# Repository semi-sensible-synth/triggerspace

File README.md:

# triggerspace

> **TESTED** - v0.042 works with some simple bodges (build notes below)
>
> **IN PROGRESS** - v0.5.0 removes the v0.042 bodges and adds optional RC reconstruction-cap
> sockets on the jack PCB's outputs to support alternative oscillators/sampler firmware; not yet fabricated or bench-verified (see
> [CHANGELOG.md](CHANGELOG.md))

This is a remix of the [NanoGris](https://github.com/Quinienl/NanoGris) trigger sequence generator (by Quinie), which in turn was based on the original [Grids](https://pichenettes.github.io/mutable-instruments-documentation/modules/grids/) hardware design by Mutable Instruments / Émilie Gillet, used under a Creative Commons ShareAlike 3.0 License (CC BY-SA 3.0).

The front panel looks something like this:

# Features
- Outputs three channels of 'topographic' drum triggers (kick, snare, hihat), with accent outputs
- Internal clock, with reset and swing
- External clock input, via triggers or MIDI clock
- Beat density (fill), X, Y and Chaos inputs to modify each pattern
- MIDI TRS-A output, General MIDI drum notes on channel 10
- MIDI TRS input accepts Type A and Type B (v0.5.0, [LPZW auto-crossover MIDI input](https://github.com/kay-lpzw/LPZW_TRS_MIDI))
- 38mA peak current draw on +12V rail (28mA idle)
- Experimental alternative firmwares: 6-voice oscillator [Gritty-osc](https://github.com/semi-sensible-synth/triggerspace/blob/main/firmware/Gritty-osc/README.md) and drum hit synth [Gritty-drumsynth](https://github.com/semi-sensible-synth/triggerspace/blob/main/firmware/Gritty-drumsynth/README.md)

## Firmware

_The stock Grids/NanoGris firmware is not compatible_ - use this: [Gritty-Grids firmware (triggerspace fork)](https://github.com/semi-sensible-synth/Gritty-Grids). Follow the instructions there to flash the firmware to your triggerspace module.

This Gritty-Grids fork:

- Supports modified Arduino Nano pin assignments used by _triggerspace_ hardware
- Sends General MIDI drum notes on channel 10 to MIDI-OUT (TRS-A)
  - GM MIDI (and Roland TR-8S) drum note numbers:
  ```
  Out 1:             36 (0x24, C1)  - bass/kick drum
  Out 2:             38 (0x26, D1)  - snare drum
  Out 3 (no accent): 42 (0x2a, F#1) - closed hi-hat
  Out 3 (accented):  46 (0x2e, Bb1) - open hi-hat
  ```
- Maps accents to MIDI note velocity: accented steps are sent at velocity 127 and
  unaccented steps at 90. Accented hi-hat steps also switch to the open hi-hat note (46).
  - Accents only exist in drum mode. With the clock output option on, Grids
    has a single common accent output, so that accent applies to all three drums.
  - In Euclidean mode there are no accents: every note is sent at velocity 127 as the
    closed hi-hat.
  - Set by `midi_accent_velocity` in `grids/grids.cc` (default on). When off, every note
    is sent at 127; the open/closed hi-hat switch still follows the accent. It can only
    be changed by recompiling for now.
  - Gritty-drumsynth sends MIDI notes the same way.

## Build options

### MIDI IN optocoupler (U8 / U9)

From v0.5.0 the MIDI input is the
[LPZW auto-crossover MIDI input](https://github.com/kay-lpzw/LPZW_TRS_MIDI) by Kay Knofe
of LPZW.modules.

It accepts TRS Type A and Type B cables with no switch. It works by using the two LEDs of a dual optocoupler in an 'anti-parallel' configuration across the tip and ring, each with its own 220R. Whichever way round the loop current flows, one LED lights, and the two open-collector outputs share one 1k pull-up (R47), so the Nano sees the same signal either way.

Fit one of these:

| Build | U8 (DIP-8 socket) | U9 (SOIC-8) | D7 | JP3, JP4 | Accepts |
|---|---|---|---|---|---|
| **Default** | HCPL-2630 or HCPL-2631 | not fitted | not fitted | as made (1-2 bridged) | Type A and B |
| SMD optocoupler | not fitted, no socket | HCPL-0630 or HCPL-0631 | not fitted | as made (1-2 bridged) | Type A and B |
| 6N138 (as v0.042) | 6N138 | not fitted | 1N4148 | cut 1-2, bridge 2-3 | Type A only |

- U9 sits inside U8's DIP-8 footprint on the back of the jack PCB, so fit U8 or U9,
  never both - a DIP socket would sit on top of U9. The HCPL-263x (DIP-8) and HCPL-063x
  (SOIC-8) have the same pinout.
- R46 (4.7k) is fitted in every build but only connected (through JP4) in the 6N138
  build, where it is the 6N138's base resistor. R51 is only used by the dual
  optocouplers; with a 6N138 it goes to an unconnected pin.
- D7 protects the 6N138's LED from reverse voltage. Don't fit it with a dual
  optocoupler: it would sit across one of the LEDs and take the current meant for the
  other, so Type B input would stop working.
- The HCPL-263x/063x is guaranteed to switch at 5mA LED current. A 5V MIDI 1.0 sender
  into a 220R receiver gives about 5mA, so worst-case parts are marginal (typical parts
  switch at about 2mA); 3.3V senders built to the MIDI Association's CA-33 values give
  about 7mA. The 6N138 needs only about 1.6mA, so it tolerates weaker Type A senders.

See [Jumpers](#jumpers) for JP3/JP4 to enable the 6N138 build (and other jumper settings).

### -5V reference: LM4040 or 5.1V zener (U5 / D8)

U5 (LM4040LP-5, TO-92) makes the -5V reference (`ref_5`) for the CV input offsets,
fed from -12V through R31 (10k). D8 is an alternative footprint in parallel with it for
a 5.1V zener diode (DO-35, e.g. BZX79C5V1 or 1N5231B), which worked well on a v0.042
build. Fit U5 or D8, not both.

- D8 sits inside U5's outline and is mounted upright: the diode body goes on the round
  pad with the cathode band at the top, and the bent lead goes into the square pad
  (marked K, to GND). The anode is on `ref_5`, because the reference is negative.
- R31 sets the zener current to about (12V - 5.1V) / 10k = 0.7mA. This is below the
  5-20mA test current of common 5.1V zeners, so expect a little less than 5.1V and a
  less stable voltage than the LM4040. The voltage shifts the CV input offsets slightly;
  it doesn't affect the triggers.

### +5V supply and power header (U4, JP5, JP6, J12)

The +5V rail (op amps, shift register, pots, trigger transistors) can come from one of
three sources. Use exactly one: don't connect two regulator outputs together.

| +5V source | U4, C11, C12 | JP5 | JP6 | Power cable |
|---|---|---|---|---|
| **U4 (L7805), default** | fitted | open | open | 10-pin or 16-pin |
| Nano's regulator | not fitted | bridged | open | 10-pin or 16-pin |
| Eurorack +5V | not fitted | open | bridged | 16-pin, from a PSU with +5V |

U4, C11 and C12 are marked "OPTIONAL" on the silkscreen. JP5 and JP6 are open as made.

- **Nano's regulator (JP5):** since v0.5.0 the Nano's VIN is fed from +12V, so its
  onboard 5V regulator is running anyway. JP5 connects the Nano's 5V pin (A1 pin 27) to
  the +5V rail, so that regulator supplies the whole module. The v0.042 module drew
  28-38mA from +12V in total, so the regulator dissipates about (12V - 5V) x 38mA =
  0.27W. With JP5 bridged, the Nano's USB port also powers the +5V rail when the module
  has no Eurorack power.
- **Eurorack +5V (JP6):** J12 is a 16-pin (2x8) footprint. Pins 11 and 12 are the
  Eurorack +5V rail, connected to the module's +5V rail through JP6. Pins 13-16 (CV and
  Gate buses) are not connected. With JP6 open, a 16-pin cable is safe whether or not
  the PSU provides +5V.
- **10-pin header in the 16-pin footprint:** a 2x5 header fits in J12 pins 1-10 (the
  end with the square pad, marked "RED!!" for the cable's -12V stripe), so 10-pin cables
  still work. The
  silkscreen outline is drawn for a 16-pin shrouded header; line up a 10-pin header's
  pin 1 with the square pad.

### RC reconstruction caps (CH*_CAP1)

The six 2-pin sockets next to the output jacks on the jack PCB (`CH1_CAP1`,
`CH1_ACC_CAP1`, `CH2_CAP1`, `CH2_ACC_CAP1`, `CH3_CAP1`, `CH3_ACC_CAP1`) take optional
capacitors to GND that filter the sigma-delta hiss from the Gritty-drumsynth firmware's
synthesised drum voices. Leave them empty for trigger outputs (Gritty-Grids firmware).
Values are still to be chosen (see TODO / IDEAS).

## Jumpers

Most solder jumpers (JP1-JP4) are shorted by a copper trace between their pads as made;
cut the trace with a craft knife to open them. JP5 and JP6 are open as made. Bridge pads
with solder to close a jumper. Pin
jumpers (J) are 2.54mm headers for jumper caps. Pin 1 of each header is the square pad.
The silkscreen next to each header repeats its settings.

Firmware and jack function settings, as shipped:

| Function | Gritty-Grids firmware (MIDI, default) | Stock Grids/NanoGris firmware (triggers) |
|---|---|---|
| Clock input to the Nano | JP2 bridged (clock on D8) | cut JP2, fit J2 (clock on D1) |
| Nano D1/TX | JP1 bridged (D1 drives MIDI OUT) | cut JP1, fit J1 (see below) |
| CLOCK / MIDI OUT jack | J6 1-2, J3 3-4 (optionally also J3 1-2) | J6 2-3, J3 1-2 |
| RND / MIDI IN jack | J8 2-3, J5 1-2, J4 3-4 | J8 1-2, J5 2-3, J4 1-2 |
| +5V source | U4 fitted, JP5 and JP6 open | same |

The jack settings are independent of the firmware: with Gritty-Grids you can still set
either jack back to a trigger output, and the MIDI clock or MIDI notes on that port are
then lost.

### Back PCB

- **JP1** (bridged) connects Nano D1/TX to the MIDI OUT line (`OUT_MIDI`, through R49
  to the jack). **JP2** (bridged) connects the clock input transistor (Q1) to D8. Both
  stay bridged for Gritty-Grids.
- **J1** connects D8 to the MIDI OUT line and **J2** connects the clock input to D1.
  The silkscreen instruction for stock firmware is "cut JP1 & JP2, bridge jumper J1,
  J2": the clock input then reaches D1, where the stock firmware reads it, and D1 is no
  longer connected to the MIDI OUT line. Don't fit J1 or J2 with JP1 and JP2 still
  bridged.
- **J5** (3-pin, to the RND / MIDI IN jack via the jack PCB): 1-2 = MIDI IN (optocoupler
  output to D0/RX), 2-3 = RND trigger output.
- **J6** (3-pin, to the CLOCK / MIDI OUT jack via the jack PCB): 1-2 = MIDI OUT (D1/TX
  through R49), 2-3 = CLOCK trigger output.
- **J9** (2-pin, silkscreen "MIDI IN" / "MIDI OUT"): pin 1 = D0/RX, pin 2 = D1/TX
  (logic level, before R49). Use it to wire up a different MIDI interface (e.g. a DIN
  socket board). If you feed a MIDI signal into pin 1, remove the J5 jumper so the
  optocoupler output doesn't drive the same line.
- **JP5** (open, below the Nano): bridge to power the +5V rail from the Nano's
  regulator. **JP6** (open, next to J12): bridge to power the +5V rail from the Eurorack
  +5V on a 16-pin cable. Fit U4, C11 and C12 only if both are open. See
  [+5V supply and power header](#5v-supply-and-power-header-u4-jp5-jp6-j12).

### Jack PCB

- **J3** (4-pin, CLOCK / MIDI OUT jack): 1-2 connects the sleeve to GND, 3-4 connects the
  ring to +5V through R50. CLOCK OUT: 1-2. MIDI OUT: 3-4; also fit 1-2 so the sleeve
  (cable shield) is grounded at the sending end, as the MIDI specification asks.
- **J4** (4-pin, RND / MIDI IN jack): 1-2 connects the sleeve to GND, 3-4 connects the
  ring to the optocoupler. RND OUT: 1-2. MIDI IN: 3-4 only; leave 1-2 open, since a MIDI
  receiver must not ground the cable shield.
- **J8** (3-pin, RND / MIDI IN jack tip): 1-2 = RND trigger output to the tip, 2-3 =
  optocoupler output to the back PCB (MIDI IN).
- **JP3** and **JP4** (3-pad solder jumpers, 1-2 bridged as made) select the MIDI IN
  optocoupler type. Leave them as made for the dual optocoupler (HCPL-263x in U8, or
  HCPL-063x in U9). For a 6N138, cut 1-2 and bridge 2-3 on both, and fit D7. See
  [MIDI IN optocoupler](#midi-in-optocoupler-u8--u9).
  - JP3 pad 2 goes to U8 pin 2 (HCPL-263x: LED 1 cathode; 6N138: LED anode). Pad 1 =
    jack ring (dual optocoupler), pad 3 = the R48 / D7 node (6N138).
  - JP4 pad 2 goes to U8 pin 7 (HCPL-263x: output 1; 6N138: transistor base). Pad 1 =
    the shared output and R47 pull-up (dual optocoupler), pad 3 = R46 4.7k to GND
    (6N138).

## Changelog

See [CHANGELOG.md](CHANGELOG.md) for the changes in each hardware revision.

## v0.042 build guide notes (bodges required !)

  - Trying to power the Nano via 5V from U4 voltage regulator to VIN pin 30 didn't work here, despite the original NanoGris design doing it this way. Upon reflection this is no surprise ... 5V isn't enough for the typical AMS1117-5.0 regulator found on a Nano (clone), which needs ~>= 6.5V input to work ! I fixed this with a bodge as follows:
    - Melt the VIN pin 30 solder joint and push it 'up' so it doesn't insert into the female header. This disconnects the Nano from the U4 regulator, but still allows U4 to power the 5V rail in the rest of the module.
    - Attach a bodge wire from the +12V rail pin on the U4 voltage regulator to the protruding VIN pin 30 (I used a single female header to make it easy to remove the Nano if required).
  - I didn't have an LM4040-5.0 on hand, but a 5.1V Zener diode seems to work well enough. From v0.5.0 it has its own footprint (D8, see [Build options](#build-options)).
  - Can optionally use an 78L50 (TO-92) voltage regulator rather than L7805 (TO-220)
  - Sometimes flashing the firmware seems to fail (can't connect to device) when the Nano is in the module, but seems to work if you take out out of the PCB to flash ¯\_(ツ)_/¯

## Modifications from the original NanoGris module

- Added MIDI-IN TRS-A jack + 6N137 optocoupler for MIDI clock sync. The original Grids always had this option as an extra jumper on the PCB - now it's broken out onto a more cluttered front panel !
- Added MIDI-OUT TRS-A - required changing the pin used for the clock in to allow use of hardware serial TX/RX, so this modules requires [custom firmware](https://github.com/semi-sensible-synth/Gritty-Grids) even if you aren't using the MIDI-OUT option.
  - I've added pin jumpers and cuttable solder jumpers to allow re-routing for stock firmware if required/desired.
- The CLOCK and RND outputs are repurposed as the TRS-A MIDI-OUT and MIDI-IN ports, respectively. Several pin jumpers can be used to choose if these act as MIDI ports or the original voltage-based trigger outputs.
- Made more space between the FILL knobs (closer to original Grids layout), use a tactile button and cap for TAP button, various tweaks to routing and front panel design

## TODO / IDEAS

- Fabricate and bench-verify v0.5.0.
- Choose the RC reconstruction-cap values (and confirm the socket footprint) by bench
  testing with the Gritty-drumsynth firmware.
- Bench-test the +5V supply options (JP5: Nano regulator, JP6: Eurorack +5V) without
  U4.
- Do we have room for mute switches/buttons on each channel ?
- Now that we are using a full 8x2 IDC power socket - can we also (optionally) connect the CV/GATE pins (eg to clock), or follow the Disting Select Bus protocol to use it for MIDI ?

### Future firmware ideas

- Disting Ex SD 6 Triggers mode, where notes span 48-53 (unaccented and accented)
- Chord/arp output over MIDI. Set the chord root/inversion to be played via one of the CV inputs, or MIDI-IN
  - Read MIDI notes from MIDI-IN, buffer the last 3 or 6 notes seen and play these for Out1-3, Accent 1-3
- (Crazier ideas: pair it with a SAM2695 or VS1053B based module/expander for GM MIDI audio out ! There seem to be NOS versions on AliExpress ....)

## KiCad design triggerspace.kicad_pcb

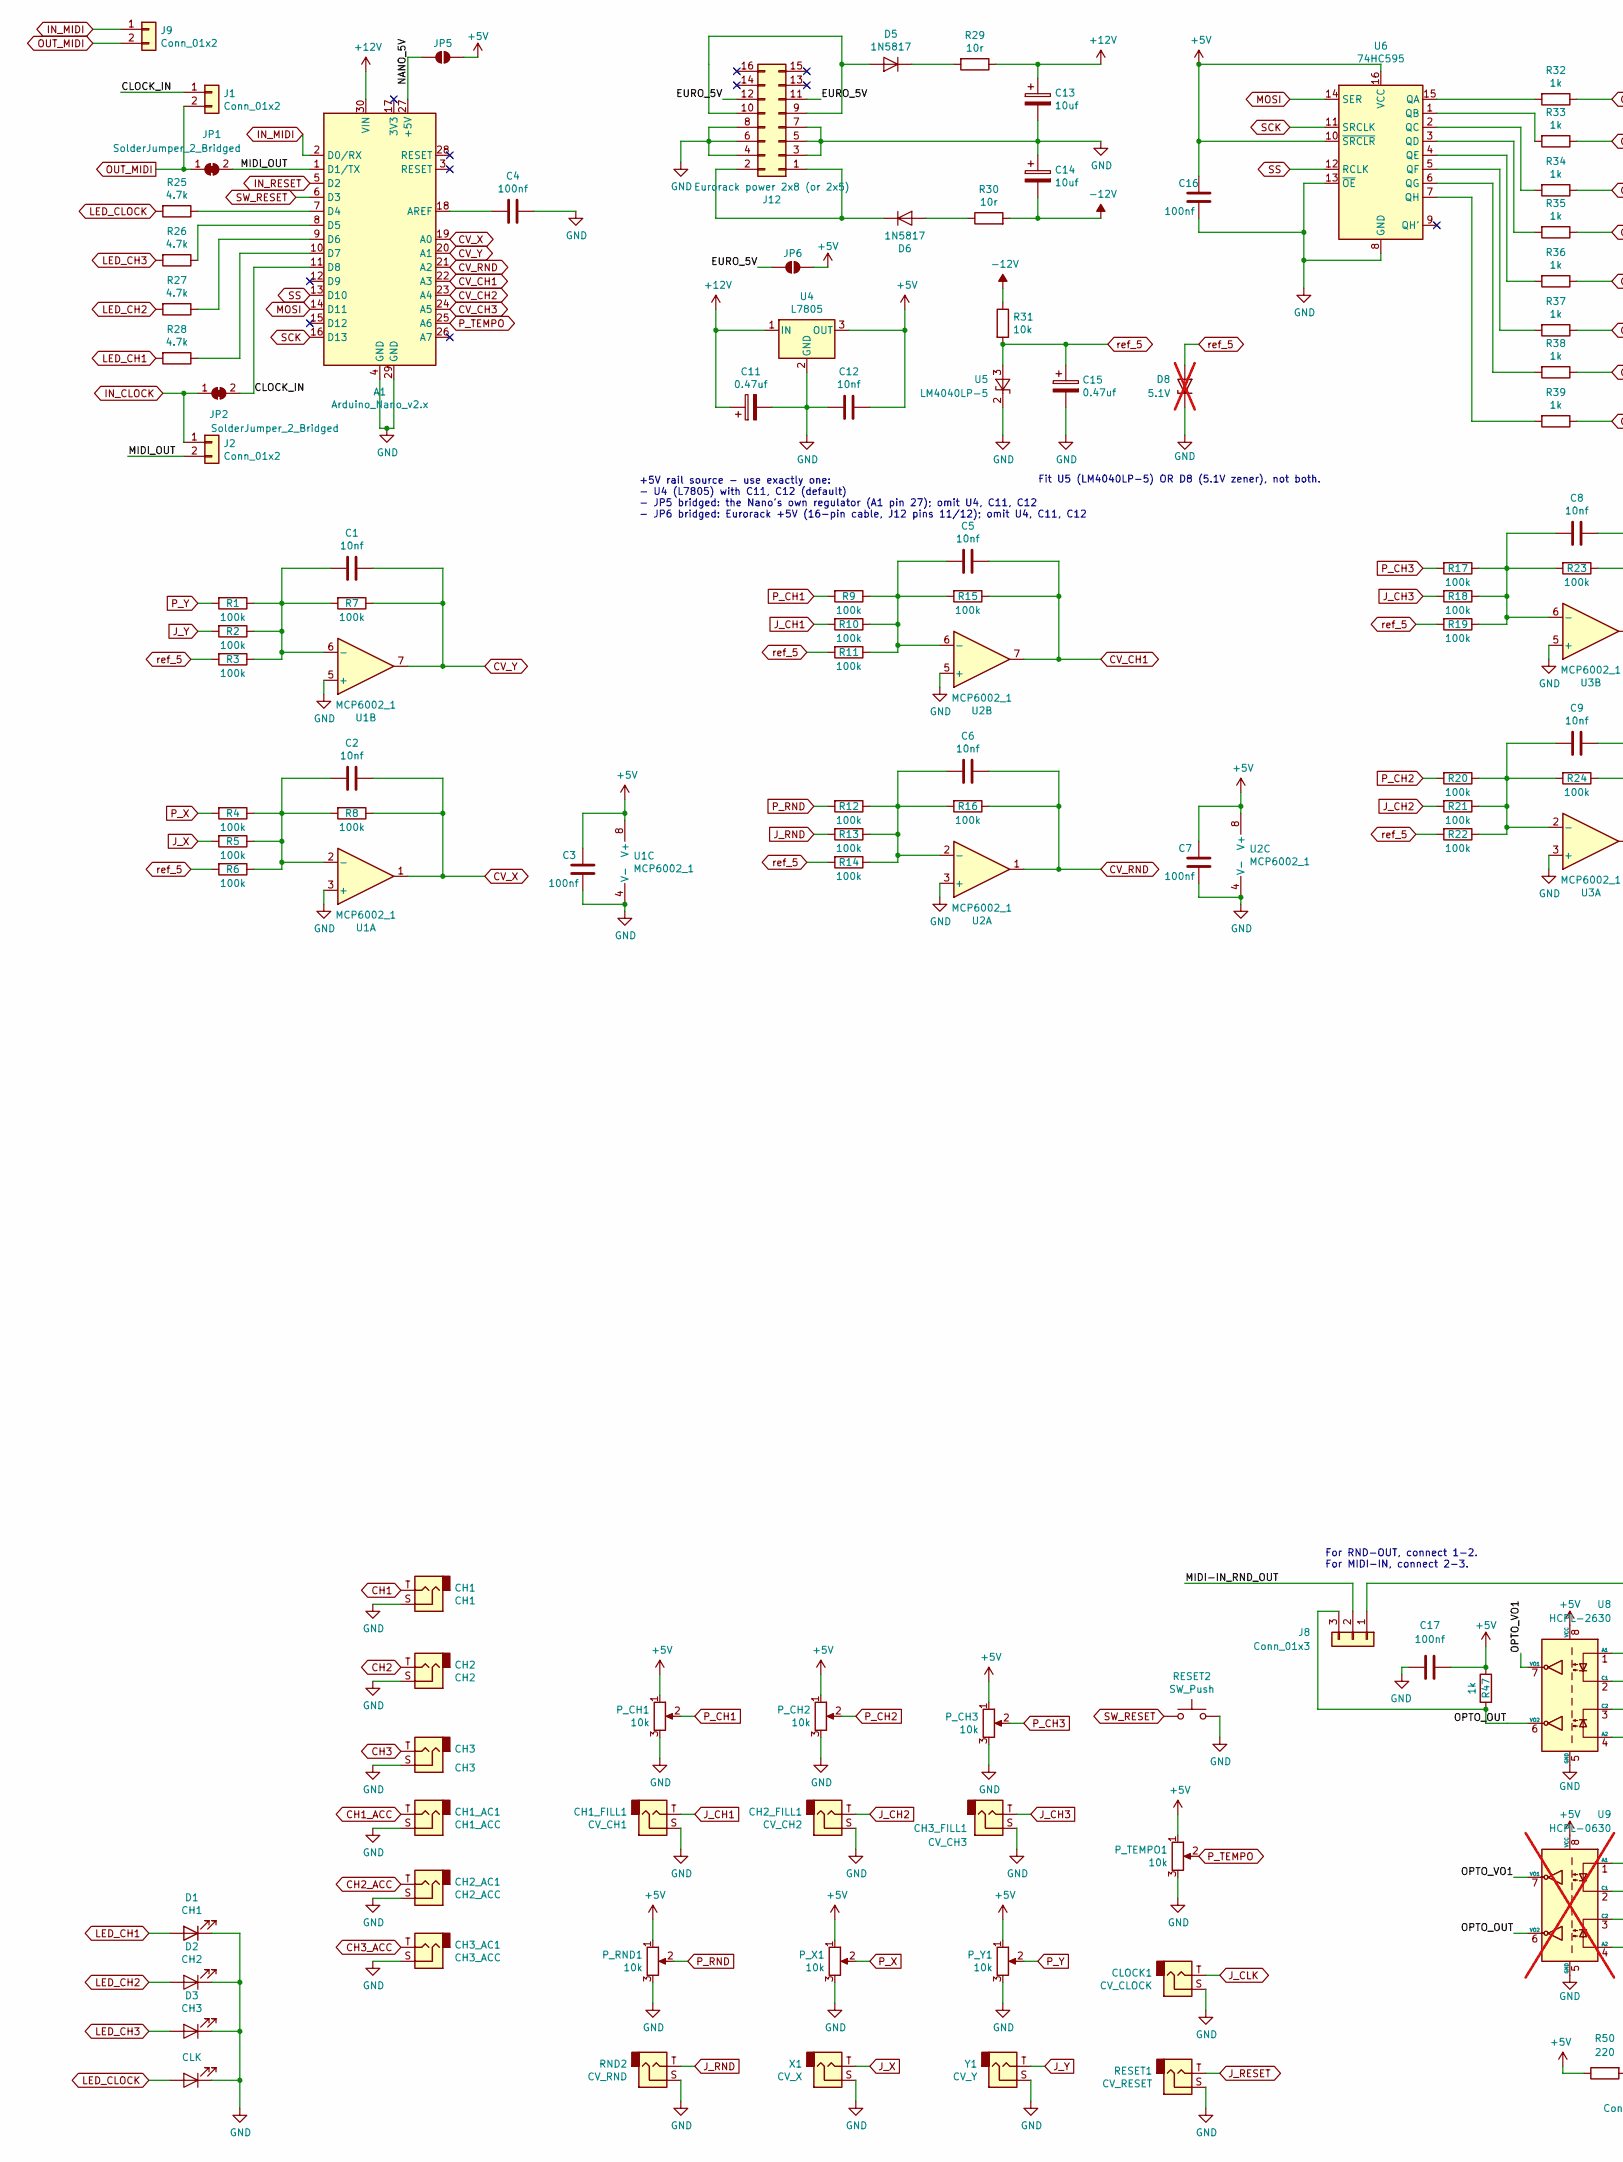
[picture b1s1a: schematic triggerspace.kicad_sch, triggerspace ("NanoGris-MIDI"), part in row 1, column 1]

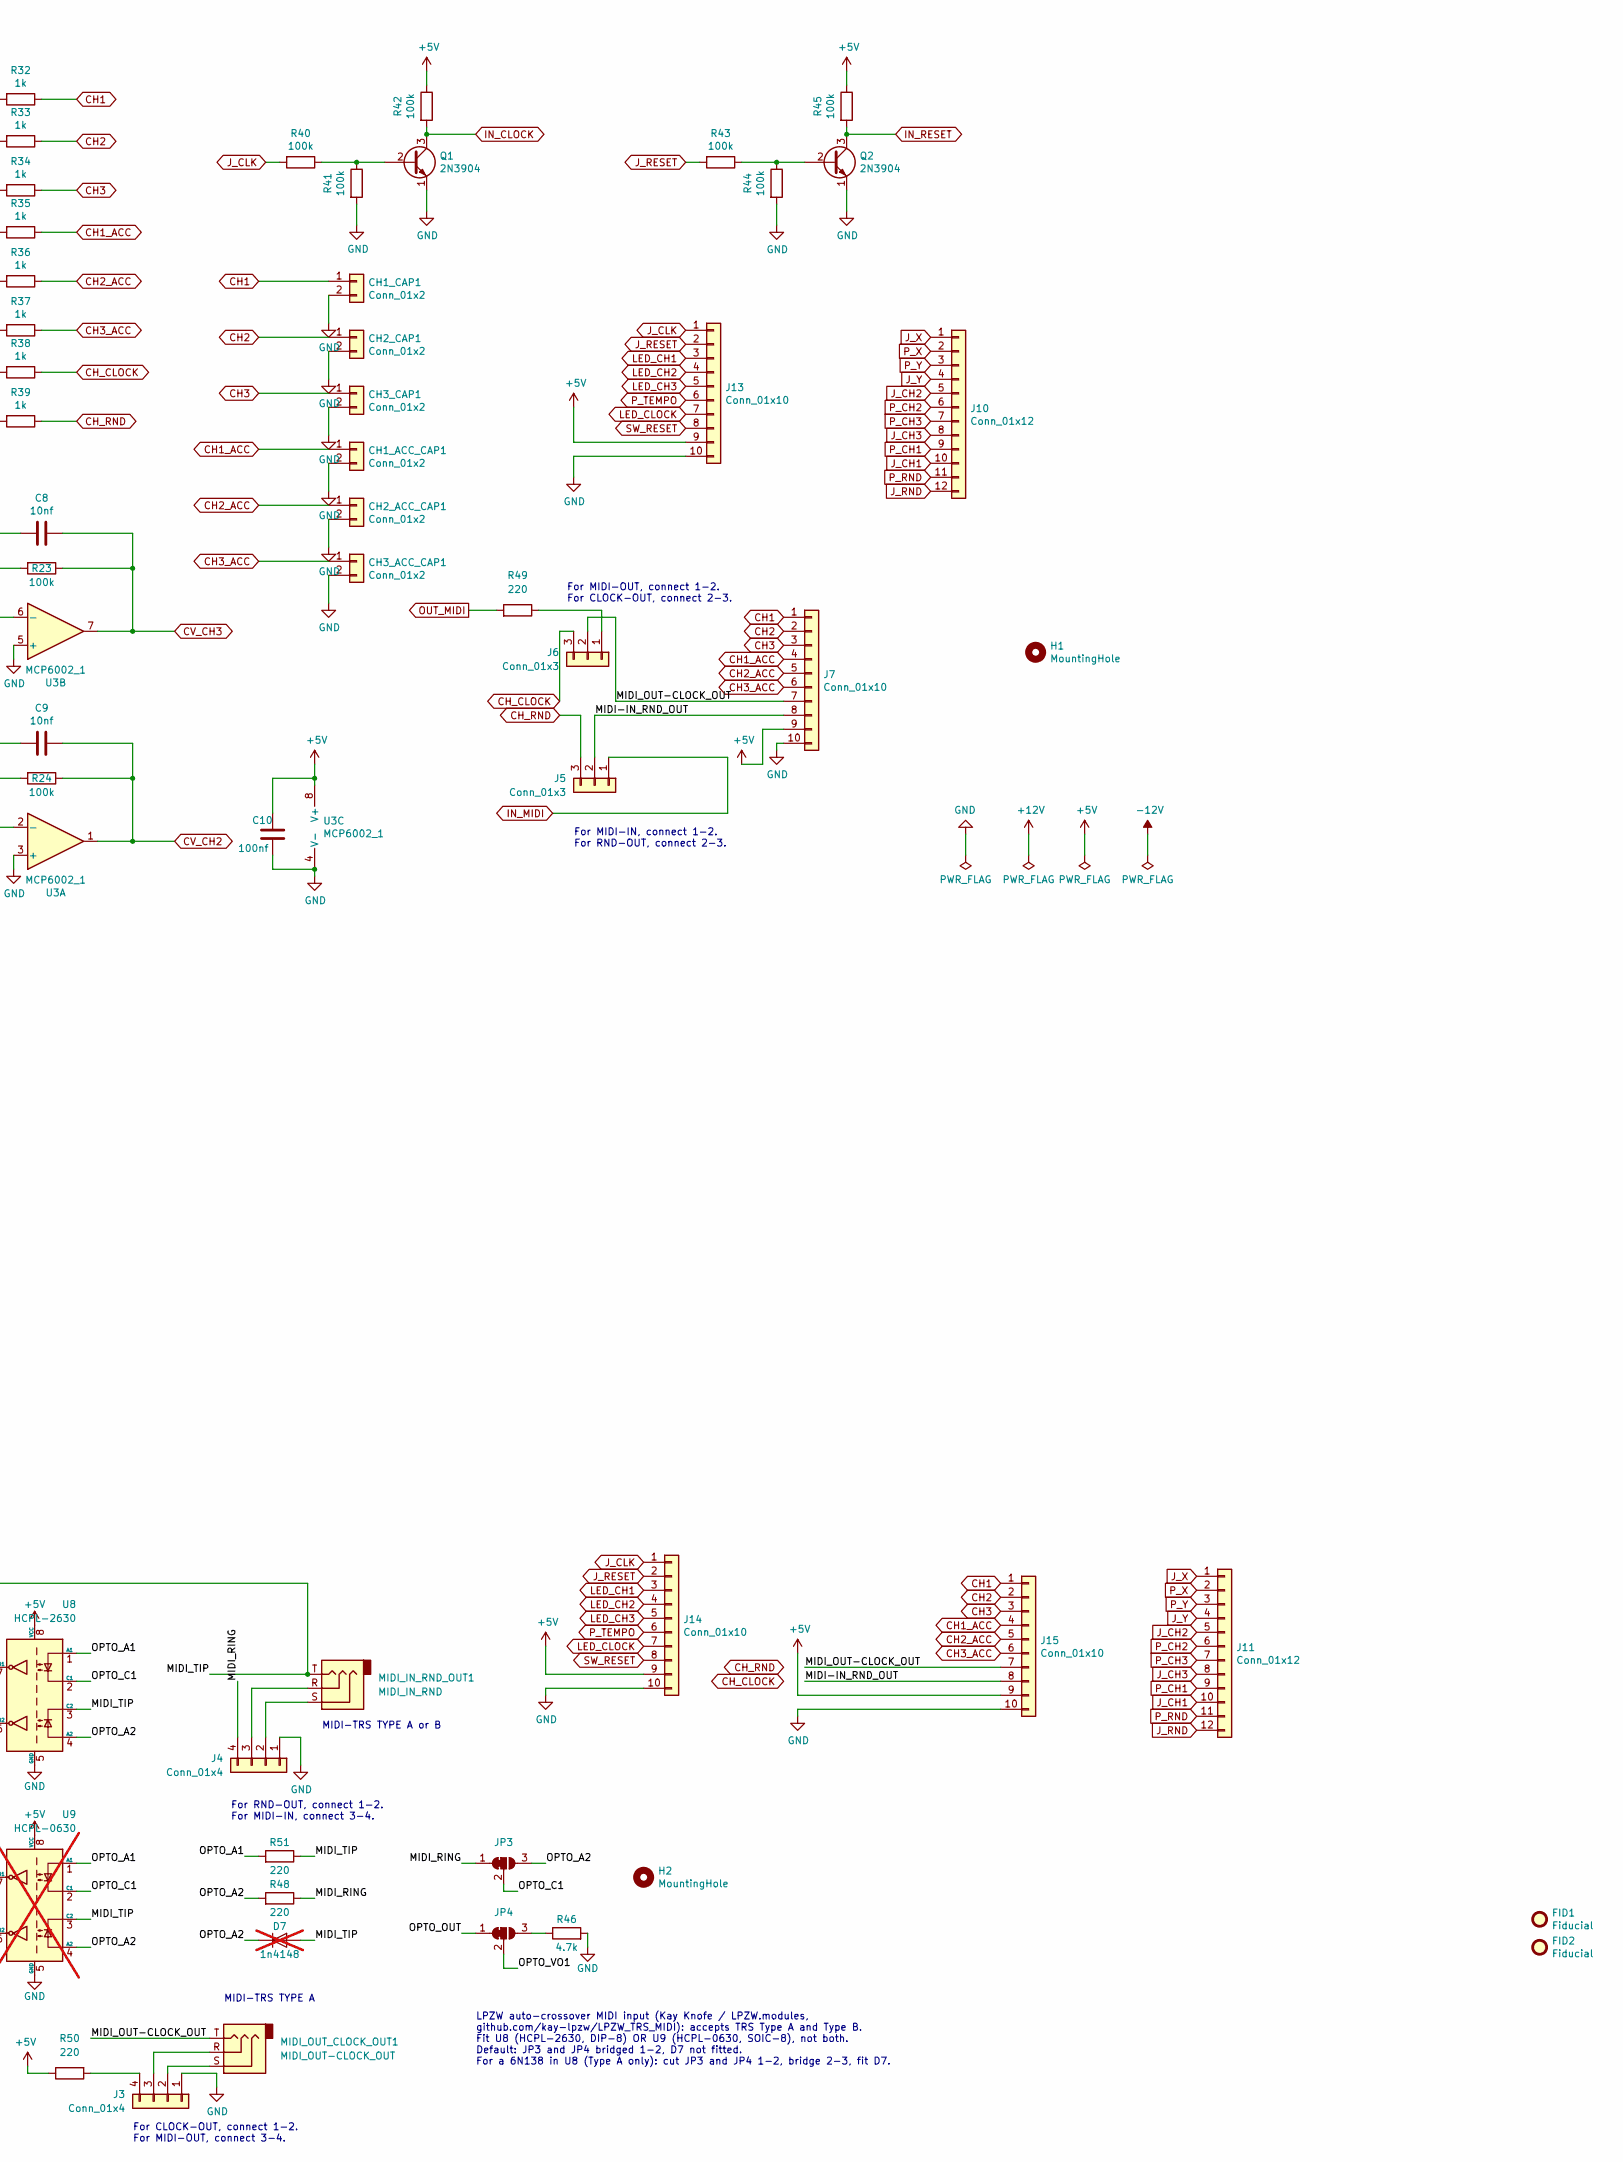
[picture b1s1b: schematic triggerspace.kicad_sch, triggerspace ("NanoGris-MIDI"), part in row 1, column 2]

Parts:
A1: Arduino_Nano_v2.x; Arduino_Nano
C1, C2, C5, C6, C8, C9, C12: 10nf; C_Disc_D5.0mm_W2.5mm_P2.50mm
C3, C4, C7, C10, C16, C17: 100nf; C_Disc_D5.0mm_W2.5mm_P2.50mm
C11, C15: 0.47uf; CP_Radial_D5.0mm_P2.50mm
C13, C14: 10uf; CP_Radial_D5.0mm_P2.50mm
CH1: CH1; Jack_3.5mm_QingPu_WQP-PJ398SM_Vertical_CircularHoles
CH1_AC1: CH1_ACC; Jack_3.5mm_QingPu_WQP-PJ398SM_Vertical_CircularHoles
CH1_ACC_CAP1, CH1_CAP1, CH2_ACC_CAP1, CH2_CAP1, CH3_ACC_CAP1, CH3_CAP1: Conn_01x2; PinSocket_1x02_P2.54mm_Vertical
CH1_FILL1: CV_CH1; Jack_3.5mm_QingPu_WQP-PJ398SM_Vertical_CircularHoles
CH2: CH2; Jack_3.5mm_QingPu_WQP-PJ398SM_Vertical_CircularHoles
CH2_AC1: CH2_ACC; Jack_3.5mm_QingPu_WQP-PJ398SM_Vertical_CircularHoles
CH2_FILL1: CV_CH2; Jack_3.5mm_QingPu_WQP-PJ398SM_Vertical_CircularHoles
CH3: CH3; Jack_3.5mm_QingPu_WQP-PJ398SM_Vertical_CircularHoles
CH3_AC1: CH3_ACC; Jack_3.5mm_QingPu_WQP-PJ398SM_Vertical_CircularHoles
CH3_FILL1: CV_CH3; Jack_3.5mm_QingPu_WQP-PJ398SM_Vertical_CircularHoles
CLOCK1: CV_CLOCK; Jack_3.5mm_QingPu_WQP-PJ398SM_Vertical_CircularHoles
D1: CH1; LED_D3.0mm
D2: CH2; LED_D3.0mm
D3: CH3; LED_D3.0mm
D4: CLK; LED_D3.0mm
D5, D6: 1N5817; D_DO-34_SOD68_P7.62mm_Horizontal
D7: 1n4148; D_DO-34_SOD68_P7.62mm_Horizontal; not fitted
D8: 5.1V; D_DO-35_SOD27_P2.54mm_Vertical_KathodeUp; not fitted
FID1: Fiducial; OSHW-Logo2_7.3x6mm_SilkScreen
FID2: Fiducial; OSHW-Logo2_14.6x12mm_SilkScreen
H1, H2: MountingHole; MountingHole_3.2mm_M3
J1, J2, J9: Conn_01x2; PinSocket_1x02_P2.54mm_Vertical
J3, J4: Conn_01x4; PinHeader_1x04_P2.54mm_Vertical
J5, J6, J8: Conn_01x3; PinHeader_1x03_P2.54mm_Vertical
J7, J13: Conn_01x10; PinSocket_1x10_P2.54mm_Vertical
J10: Conn_01x12; PinSocket_1x12_P2.54mm_Vertical
J11: Conn_01x12; PinHeader_1x12_P2.54mm_Vertical
J12: Eurorack power 2x8 (or 2x5); IDC-Header_2x08_P2.54mm_Vertical
J14, J15: Conn_01x10; PinHeader_1x10_P2.54mm_Vertical
JP1, JP2: SolderJumper_2_Bridged; SolderJumper-2_P1.3mm_Bridged_RoundedPad1.0x1.5mm
JP3, JP4: SolderJumper_3_Bridged12; SolderJumper-3_P1.3mm_Bridged12_RoundedPad1.0x1.5mm_NumberL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
JP5, JP6: SolderJumper_2_Open; SolderJumper-2_P1.3mm_Open_RoundedPad1.0x1.5mm
MIDI_IN_RND_OUT1: MIDI_IN_RND; Jack_3.5mm_QingPu_WQP-PJ398SM_Vertical_CircularHoles
MIDI_OUT_CLOCK_OUT1: MIDI_OUT-CLOCK_OUT; Jack_3.5mm_QingPu_WQP-PJ398SM_Vertical_CircularHoles
P_CH1, P_CH2, P_CH3: 10k; Potentiometer_Alps_RK09K_Single_Vertical_round
P_RND1: 10k; Potentiometer_Alps_RK09K_Single_Vertical_round
P_TEMPO1: 10k; Potentiometer_Alps_RK09K_Single_Vertical_round
P_X1: 10k; Potentiometer_Alps_RK09K_Single_Vertical_round
P_Y1: 10k; Potentiometer_Alps_RK09K_Single_Vertical_round
Q1, Q2: 2N3904; TO-92_Wide
R1, R2, R3, R4, R5, R6, R7, R8, R9, R10, R11, R12, R13, R14, R15, R16, R17, R18, R19, R20, R21, R22, R23, R24, R40, R41, R42, R43, R44, R45: 100k; R_Axial_DIN0204_L3.6mm_D1.6mm_P7.62mm_Horizontal
R25, R26, R27, R28: 4.7k; R_Axial_DIN0207_L6.3mm_D2.5mm_P7.62mm_Horizontal
R29: 10r; R_Axial_DIN0204_L3.6mm_D1.6mm_P2.54mm_Vertical
R30: 10r; R_Axial_DIN0204_L3.6mm_D1.6mm_P7.62mm_Horizontal
R31: 10k; R_Axial_DIN0204_L3.6mm_D1.6mm_P7.62mm_Horizontal
R32, R33, R34, R35, R36, R37, R38, R39, R47: 1k; R_Axial_DIN0204_L3.6mm_D1.6mm_P7.62mm_Horizontal
R46: 4.7k; R_Axial_DIN0204_L3.6mm_D1.6mm_P5.08mm_Horizontal
R48, R49, R50, R51: 220; R_Axial_DIN0204_L3.6mm_D1.6mm_P7.62mm_Horizontal
RESET1: CV_RESET; Jack_3.5mm_QingPu_WQP-PJ398SM_Vertical_CircularHoles
RESET2: SW_Push; SW_PUSH_6mm
RND2: CV_RND; Jack_3.5mm_QingPu_WQP-PJ398SM_Vertical_CircularHoles
U1, U2, U3: MCP6002_1; DIP-8_W7.62mm
U4: L7805; TO-220-3_Horizontal_TabDown
U5: LM4040LP-5; TO-92_Wide
U6: 74HC595; DIP-16_W7.62mm
U8: HCPL-2630; DIP-8_W7.62mm_Socket_LongPads
U9: HCPL-0630; SOIC-8_3.9x4.9mm_P1.27mm; not fitted
X1: CV_X; Jack_3.5mm_QingPu_WQP-PJ398SM_Vertical_CircularHoles
Y1: CV_Y; Jack_3.5mm_QingPu_WQP-PJ398SM_Vertical_CircularHoles

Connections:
+5V: C3.1, C7.1, C10.1, C12.1, C16.1, C17.1, J7.9, J13.9, J14.9, J15.9, JP5.2 (B), JP6.2 (B), P_CH1.1, P_CH2.1, P_CH3.1, P_RND1.1, P_TEMPO1.1, P_X1.1, P_Y1.1, R42.1, R45.1, R47.1, R50.1, U1.8 (V+), U2.8 (V+), U3.8 (V+), U4.3 (OUT), U6.10 (~SRCLR), U6.16 (VCC), U8.8 (VCC), U9.8 (VCC)
+12V: A1.30 (VIN), C11.1, C13.1, R29.1, U4.1 (IN)
-12V: C14.2, R30.2, R31.1
/CLOCK_IN: A1.11 (D8), J1.1, JP2.2 (B)
/EURO_5V: J12.11, J12.12, JP6.1 (A)
/MIDI-IN_RND_OUT: J5.2, J7.8, J8.2, J15.8
/MIDI_OUT: A1.1 (D1/TX), J2.2, JP1.2 (B)
/MIDI_OUT-CLOCK_OUT: J6.2, J7.7, J15.7, MIDI_OUT_CLOCK_OUT1.T
/MIDI_RING: J4.4, JP3.1 (A), R48.1
/MIDI_TIP: D7.2 (A), J8.1, MIDI_IN_RND_OUT1.T, R51.1, U8.3 (C2), U9.3 (C2)
/NANO_5V: A1.27 (+5V), JP5.1 (A)
/OPTO_A1: R51.2, U8.1 (NC), U9.1 (A1)
/OPTO_A2: D7.1 (K), JP3.3 (B), R48.2, U8.4 (NC), U9.4 (A2)
/OPTO_C1: JP3.2 (C), U8.2 (C1), U9.2 (C1)
/OPTO_OUT: J8.3, JP4.1 (A), R47.2, U8.6 (VO2), U9.6 (VO2)
/OPTO_VO1: JP4.2 (C), U8.7 (VO1), U9.7 (VO1)
CH1: CH1.T, CH1_CAP1.1, J7.1, J15.1, R32.1
CH1_ACC: CH1_AC1.T, CH1_ACC_CAP1.1, J7.4, J15.4, R35.1
CH2: CH2.T, CH2_CAP1.1, J7.2, J15.2, R33.1
CH2_ACC: CH2_AC1.T, CH2_ACC_CAP1.1, J7.5, J15.5, R36.1
CH3: CH3.T, CH3_CAP1.1, J7.3, J15.3, R34.1
CH3_ACC: CH3_AC1.T, CH3_ACC_CAP1.1, J7.6, J15.6, R37.1
CH_CLOCK: J6.3, R38.1
CH_RND: J5.3, R39.1
CV_CH1: A1.22 (A3), C5.1, R15.1, U2.7
CV_CH2: A1.23 (A4), C9.1, R24.1, U3.1
CV_CH3: A1.24 (A5), C8.1, R23.1, U3.7
CV_RND: A1.21 (A2), C6.1, R16.1, U2.1
CV_X: A1.19 (A0), C2.1, R8.1, U1.1
CV_Y: A1.20 (A1), C1.1, R7.1, U1.7
GND: A1.4 (GND), A1.29 (GND), C3.2, C4.1, C7.2, C10.2, C11.2, C12.2, C13.2, C14.1, C15.2, C16.2, C17.2, CH1.S, CH1_AC1.S, CH1_ACC_CAP1.2, CH1_CAP1.2, CH1_FILL1.S, CH2.S, CH2_AC1.S, CH2_ACC_CAP1.2, CH2_CAP1.2, CH2_FILL1.S, CH3.S, CH3_AC1.S, CH3_ACC_CAP1.2, CH3_CAP1.2, CH3_FILL1.S, CLOCK1.S, D1.1 (K), D2.1 (K), D3.1 (K), D4.1 (K), D8.1 (K), J3.1, J4.1, J7.10, J12.3, J12.4, J12.5, J12.6, J12.7, J12.8, J13.10, J14.10, J15.10, P_CH1.3, P_CH2.3, P_CH3.3, P_RND1.3, P_TEMPO1.3, P_X1.3, P_Y1.3, Q1.1 (E), Q2.1 (E), R41.2, R44.2, R46.2, RESET1.S, RESET2.2, RND2.S, U1.3 (+), U1.4 (V-), U1.5 (+), U2.3 (+), U2.4 (V-), U2.5 (+), U3.3 (+), U3.4 (V-), U3.5 (+), U4.2 (GND), U5.2 (K), U6.8 (GND), U6.13 (~OE), U8.5 (GND), U9.5 (GND), X1.S, Y1.S
IN_CLOCK: J2.1, JP2.1 (A), Q1.3 (C), R42.2
IN_MIDI: A1.2 (D0/RX), J5.1, J9.1
IN_RESET: A1.5 (D2), Q2.3 (C), R45.2
J_CH1: CH1_FILL1.T, J10.10, J11.10, R10.2
J_CH2: CH2_FILL1.T, J10.5, J11.5, R21.2
J_CH3: CH3_FILL1.T, J10.8, J11.8, R18.2
J_CLK: CLOCK1.T, J13.1, J14.1, R40.2
J_RESET: J13.2, J14.2, R43.2, RESET1.T
J_RND: J10.12, J11.12, R13.2, RND2.T
J_X: J10.1, J11.1, R5.2, X1.T
J_Y: J10.4, J11.4, R2.2, Y1.T
LED_CH1: D1.2 (A), J13.3, J14.3, R28.2
LED_CH2: D2.2 (A), J13.4, J14.4, R27.2
LED_CH3: D3.2 (A), J13.5, J14.5, R26.2
LED_CLOCK: D4.2 (A), J13.7, J14.7, R25.2
MOSI: A1.14 (D11), U6.14 (SER)
unnamed: A1.18 (AREF), C4.2
unnamed: A1.7 (D4), R25.1
unnamed: A1.8 (D5), R26.1
unnamed: A1.9 (D6), R27.1
unnamed: A1.10 (D7), R28.1
unnamed: D5.2 (A), J12.9, J12.10
unnamed: D5.1 (K), R29.2
unnamed: D6.2 (A), R30.1
unnamed: D6.1 (K), J12.1, J12.2
unnamed: J3.2, MIDI_OUT_CLOCK_OUT1.S
unnamed: J3.3, MIDI_OUT_CLOCK_OUT1.R
unnamed: J3.4, R50.2
unnamed: J4.2, MIDI_IN_RND_OUT1.S
unnamed: J4.3, MIDI_IN_RND_OUT1.R
unnamed: J6.1, R49.1
unnamed: JP4.3 (B), R46.1
unnamed: Q1.2 (B), R40.1, R41.1
unnamed: Q2.2 (B), R43.1, R44.1
unnamed: C2.2, R4.1, R5.1, R6.1, R8.2, U1.2 (-)
unnamed: C1.2, R1.1, R2.1, R3.1, R7.2, U1.6 (-)
unnamed: C6.2, R12.1, R13.1, R14.1, R16.2, U2.2 (-)
unnamed: C5.2, R9.1, R10.1, R11.1, R15.2, U2.6 (-)
unnamed: C9.2, R20.1, R21.1, R22.1, R24.2, U3.2 (-)
unnamed: C8.2, R17.1, R18.1, R19.1, R23.2, U3.6 (-)
unnamed: R32.2, U6.15 (QA)
unnamed: R33.2, U6.1 (QB)
unnamed: R34.2, U6.2 (QC)
unnamed: R35.2, U6.3 (QD)
unnamed: R36.2, U6.4 (QE)
unnamed: R37.2, U6.5 (QF)
unnamed: R38.2, U6.6 (QG)
unnamed: R39.2, U6.7 (QH)
OUT_MIDI: J1.2, J9.2, JP1.1 (A), R49.2
P_CH1: J10.9, J11.9, P_CH1.2, R9.2
P_CH2: J10.6, J11.6, P_CH2.2, R20.2
P_CH3: J10.7, J11.7, P_CH3.2, R17.2
P_RND: J10.11, J11.11, P_RND1.2, R12.2
P_TEMPO: A1.25 (A6), J13.6, J14.6, P_TEMPO1.2
P_X: J10.2, J11.2, P_X1.2, R4.2
P_Y: J10.3, J11.3, P_Y1.2, R1.2
SCK: A1.16 (D13), U6.11 (SRCLK)
SS: A1.13 (D10), U6.12 (RCLK)
SW_RESET: A1.6 (D3), J13.8, J14.8, RESET2.1
ref_5: C15.1, D8.2 (A), R3.2, R6.2, R11.2, R14.2, R19.2, R22.2, R31.2, U5.3 (A)

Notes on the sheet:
For MIDI-OUT, connect 1-2. For CLOCK-OUT, connect 2-3.
For RND-OUT, connect 1-2. For MIDI-IN, connect 3-4.
For MIDI-IN, connect 1-2. For RND-OUT, connect 2-3.
For CLOCK-OUT, connect 1-2. For MIDI-OUT, connect 3-4.
MIDI-TRS TYPE A
For RND-OUT, connect 1-2. For MIDI-IN, connect 2-3.
MIDI-TRS TYPE A or B
LPZW auto-crossover MIDI input (Kay Knofe / LPZW.modules, github.com/kay-lpzw/LPZW_TRS_MIDI): accepts TRS Type A and Type B. Fit U8 (HCPL-2630, DIP-8) OR U9 (HCPL-0630, SOIC-8), not both. Default: JP3 and JP4 bridged 1-2, D7 not fitted. For a 6N138 in U8 (Type A only): cut JP3 and JP4 1-2, bridge 2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
Fit U5 (LM4040LP-5) OR D8 (5.1V zener), not both.
+5V rail source - use exactly one: - U4 (L7805) with C11, C12 (default) - JP5 bridged: the Nano's own regulator (A1 pin 27); omit U4, C11, C12 - JP6 bridged: Eurorack +5V (16-pin cable, J12 pins 11/12); omit U4, C11, C12

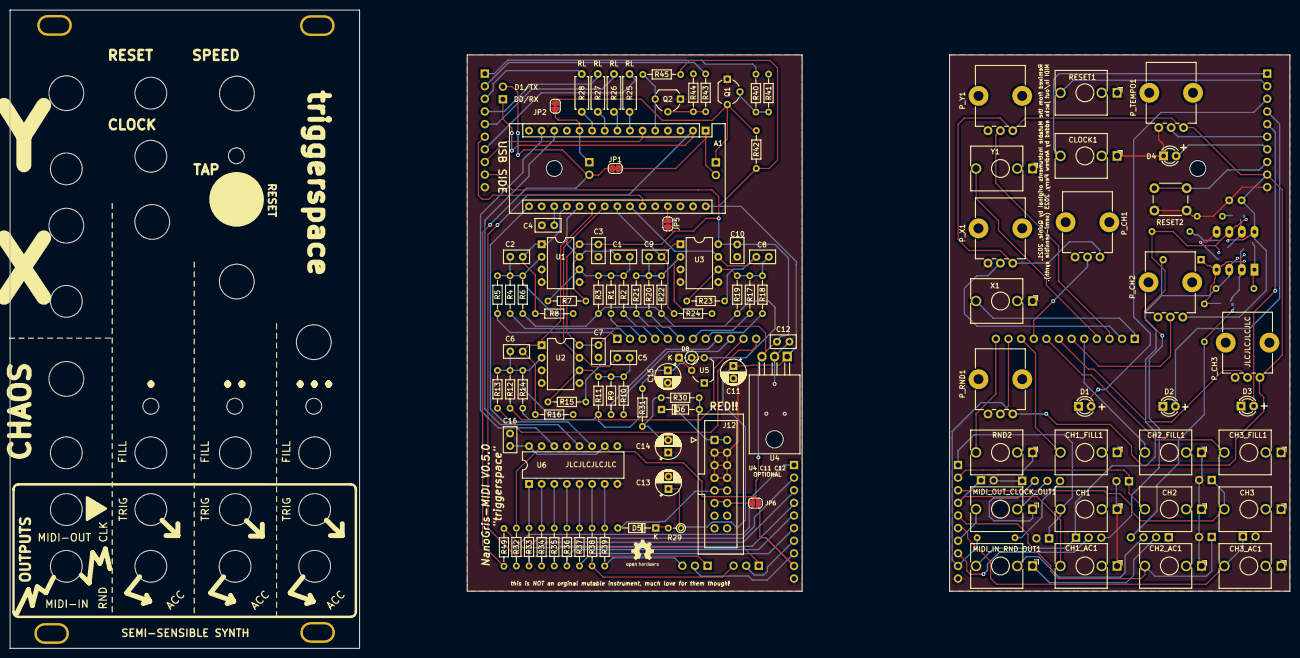
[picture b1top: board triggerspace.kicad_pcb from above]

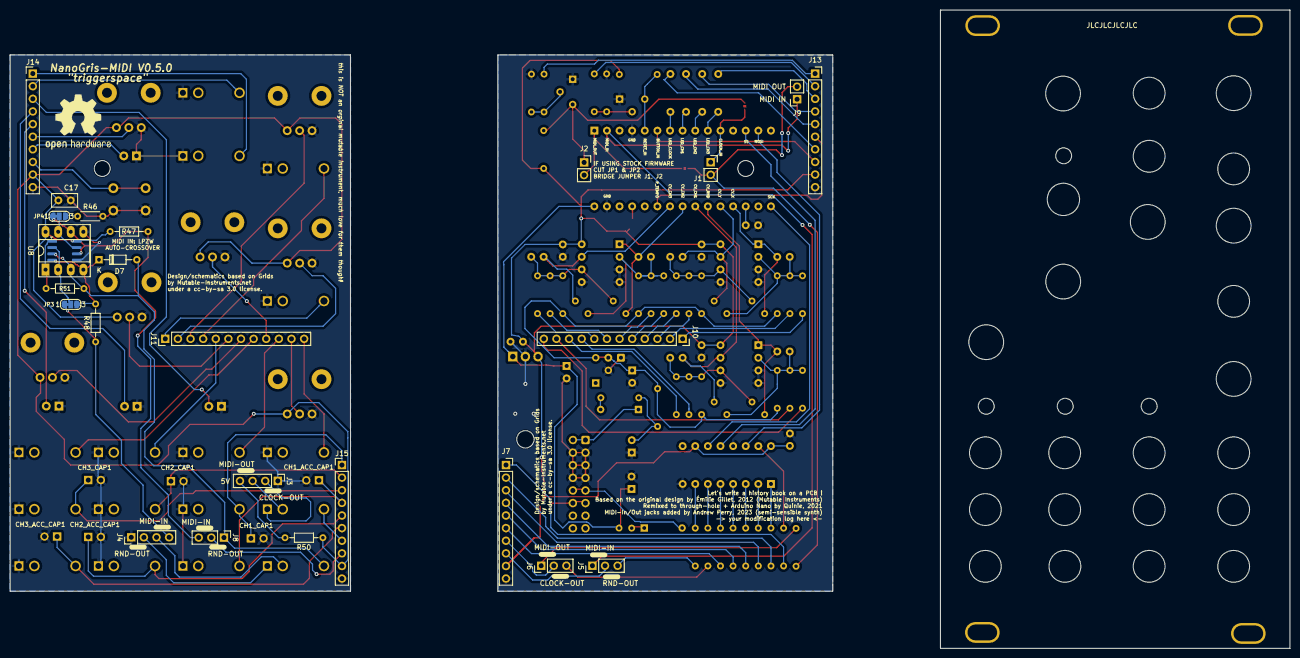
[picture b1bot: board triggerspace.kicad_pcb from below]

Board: 2 copper layers, 257.6 x 128.5 mm, 170 parts (32 on the bottom side), 91 nets.

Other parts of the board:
H1#2, H2#2, H3, H4, H5, H6, H7, H8, H9, H10, H11, H12, H13, H14, H15, H16, H17: MountingHole; MountingHole_6mm
H18, H19, H20, H21: MountingHole; MountingHole_3mm
H22, H23, H24, H25, H26, H27, H28: MountingHole; MountingHole_8.4mm_M8

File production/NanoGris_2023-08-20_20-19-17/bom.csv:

Designator,Footprint,Quantity,Value,LCSC Part #
"_4, _3, _2, ",,4,,
A1,Arduino_Nano,1,Arduino_Nano_v2.x,
"C1, C12, C2, C5, C6, C8, C9",C_Disc_D5.0mm_W2.5mm_P2.50mm,7,10nf,
"C10, C16, C17, C3, C4, C7",C_Disc_D5.0mm_W2.5mm_P2.50mm,6,100nf,
"C11, C15",CP_Radial_D5.0mm_P2.50mm,2,0.47uf,
"C13, C14",CP_Radial_D5.0mm_P2.50mm,2,10uf,
CH1,Jack_3.5mm_QingPu_WQP-PJ398SM_Vertical_CircularHoles,1,CH1,
CH1_AC1,Jack_3.5mm_QingPu_WQP-PJ398SM_Vertical_CircularHoles,1,CH1_ACC,
CH1_FILL1,Jack_3.5mm_QingPu_WQP-PJ398SM_Vertical_CircularHoles,1,CV_CH1,
CH2,Jack_3.5mm_QingPu_WQP-PJ398SM_Vertical_CircularHoles,1,CH2,
CH2_AC1,Jack_3.5mm_QingPu_WQP-PJ398SM_Vertical_CircularHoles,1,CH2_ACC,
CH2_FILL1,Jack_3.5mm_QingPu_WQP-PJ398SM_Vertical_CircularHoles,1,CV_CH2,
CH3,Jack_3.5mm_QingPu_WQP-PJ398SM_Vertical_CircularHoles,1,CH3,
CH3_AC1,Jack_3.5mm_QingPu_WQP-PJ398SM_Vertical_CircularHoles,1,CH3_ACC,
CH3_FILL1,Jack_3.5mm_QingPu_WQP-PJ398SM_Vertical_CircularHoles,1,CV_CH3,
CLK1,Jack_3.5mm_QingPu_WQP-PJ398SM_Vertical_CircularHoles,1,ClockOutput,
CLOCK1,Jack_3.5mm_QingPu_WQP-PJ398SM_Vertical_CircularHoles,1,CV_CLOCK,
D1,LED_D3.0mm,1,CH1,
D2,LED_D3.0mm,1,CH2,
D3,LED_D3.0mm,1,CH3,
D4,LED_D3.0mm,1,CLK,
"D5, D6",D_DO-34_SOD68_P7.62mm_Horizontal,2,1N5817,
D7,D_DO-34_SOD68_P7.62mm_Horizontal,1,1n4148,
FID2,OSHW-Logo2_14.6x12mm_SilkScreen,1,Fiducial,
"H1_2, H2_2",MountingHole_3.2mm_M3,2,MountingHole,
"J1, J2, J4",PinSocket_1x02_P2.54mm_Vertical,3,Conn_01x2,
J10,PinSocket_1x12_P2.54mm_Vertical,1,Conn_01x12,
J11,PinHeader_1x12_P2.54mm_Vertical,1,Conn_01x12,
J12,IDC-Header_2x05_P2.54mm_Vertical,1,Conn_02x05_Odd_Even,
"J13, J7",PinSocket_1x10_P2.54mm_Vertical,2,Conn_01x10,
"J14, J15",PinHeader_1x10_P2.54mm_Vertical,2,Conn_01x10,
J3,PinHeader_1x02_P2.54mm_Vertical,1,Conn_01x2,
"JP1, JP2",SolderJumper-2_P1.3mm_Bridged_RoundedPad1.0x1.5mm,2,SolderJumper_2_Bridged,
MIDI_IN1,Jack_3.5mm_QingPu_WQP-PJ398SM_Vertical_CircularHoles,1,MIDI_IN,
MIDI_OUT1,Jack_3.5mm_QingPu_WQP-PJ398SM_Vertical_CircularHoles,1,MIDI_OUT,
"P_CH1, P_CH2, P_CH3, P_RND1, P_TEMPO1, P_X1, P_Y1",Potentiometer_Alps_RK09K_Single_Vertical_round,7,10k,
"Q1, Q2",TO-92_Wide,2,2N3904,
"R1, R10, R11, R12, R13, R14, R15, R16, R17, R18, R19, R2, R20, R21, R22, R23, R24, R3, R4, R40, R41, R42, R43, R44, R45, R5, R6, R7, R8, R9",R_Axial_DIN0204_L3.6mm_D1.6mm_P7.62mm_Horizontal,30,100k,
"R25, R26, R27, R28",R_Axial_DIN0207_L6.3mm_D2.5mm_P7.62mm_Horizontal,4,100r,
"R29, R30",R_Axial_DIN0204_L3.6mm_D1.6mm_P7.62mm_Horizontal,2,10r,
R31,R_Axial_DIN0204_L3.6mm_D1.6mm_P7.62mm_Horizontal,1,10k,
"R32, R33, R34, R35, R36, R37, R38, R39",R_Axial_DIN0204_L3.6mm_D1.6mm_P7.62mm_Horizontal,8,1k,
R46,R_Axial_DIN0204_L3.6mm_D1.6mm_P7.62mm_Horizontal,1,4.7k,
"R47, R48, R49, R50",R_Axial_DIN0204_L3.6mm_D1.6mm_P7.62mm_Horizontal,4,220,
RESET1,Jack_3.5mm_QingPu_WQP-PJ398SM_Vertical_CircularHoles,1,CV_RESET,
RESET2,SW_PUSH_6mm,1,SW_Push,
RND1,Jack_3.5mm_QingPu_WQP-PJ398SM_Vertical_CircularHoles,1,RandomGate,
RND2,Jack_3.5mm_QingPu_WQP-PJ398SM_Vertical_CircularHoles,1,CV_RND,
"U1, U2, U3",DIP-8_W7.62mm,3,MCP6002_1,
U4,TO-220-3_Vertical,1,L7805,
U5,TO-92_Wide,1,LM4040LP-5,
U6,DIP-16_W7.62mm,1,74HC595,
U8,DIP-8_W7.62mm_Socket_LongPads,1,6N138,
X1,Jack_3.5mm_QingPu_WQP-PJ398SM_Vertical_CircularHoles,1,CV_X,
Y1,Jack_3.5mm_QingPu_WQP-PJ398SM_Vertical_CircularHoles,1,CV_Y,

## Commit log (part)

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2023-03-12 Clean front panel changes
2023-08-20 Updated with MIDI-TRS ports, numerous tweaks.
    Moved front panel into main PCB design, remove old panels and gerbers that will no longer fit this design.
2023-08-20 Generated new iBOM.
2023-08-27 Change MIDI ports to reuse clock out/rnd out ports.
    Jumpers to select if we use MIDI or clock out / rnd.
    Moved FILL knobs to a more ergonomic arrangement.
    General polish to front panel.
2023-08-27 Generate iBOM.
    Exclude some extraneous items from the BOM.
2023-08-27 Remove soldermask layers over front panel.
    We will go for a black panel in the first instance, since it seems the gerber viewer doesn't render the silkscreen when it's not on top of solder mask. For JLC bare aluminium panels we should cut the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
2023-08-27 Generate gerbers and black/white front panel.
2023-08-27 Remove unused files.
    Old BOM and older KiCad files.
2023-08-27 Change naming to 'triggerspace' in most places
2023-08-27 Add a front panel image
2024-12-31 v0.042 release.
    Update README with build notes.
    Add schematic pdf.
    KiCad files re-saved with version 8.0

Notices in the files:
triggerspace.kicad_pcb:
under a cc-by-sa 3.0 license.
